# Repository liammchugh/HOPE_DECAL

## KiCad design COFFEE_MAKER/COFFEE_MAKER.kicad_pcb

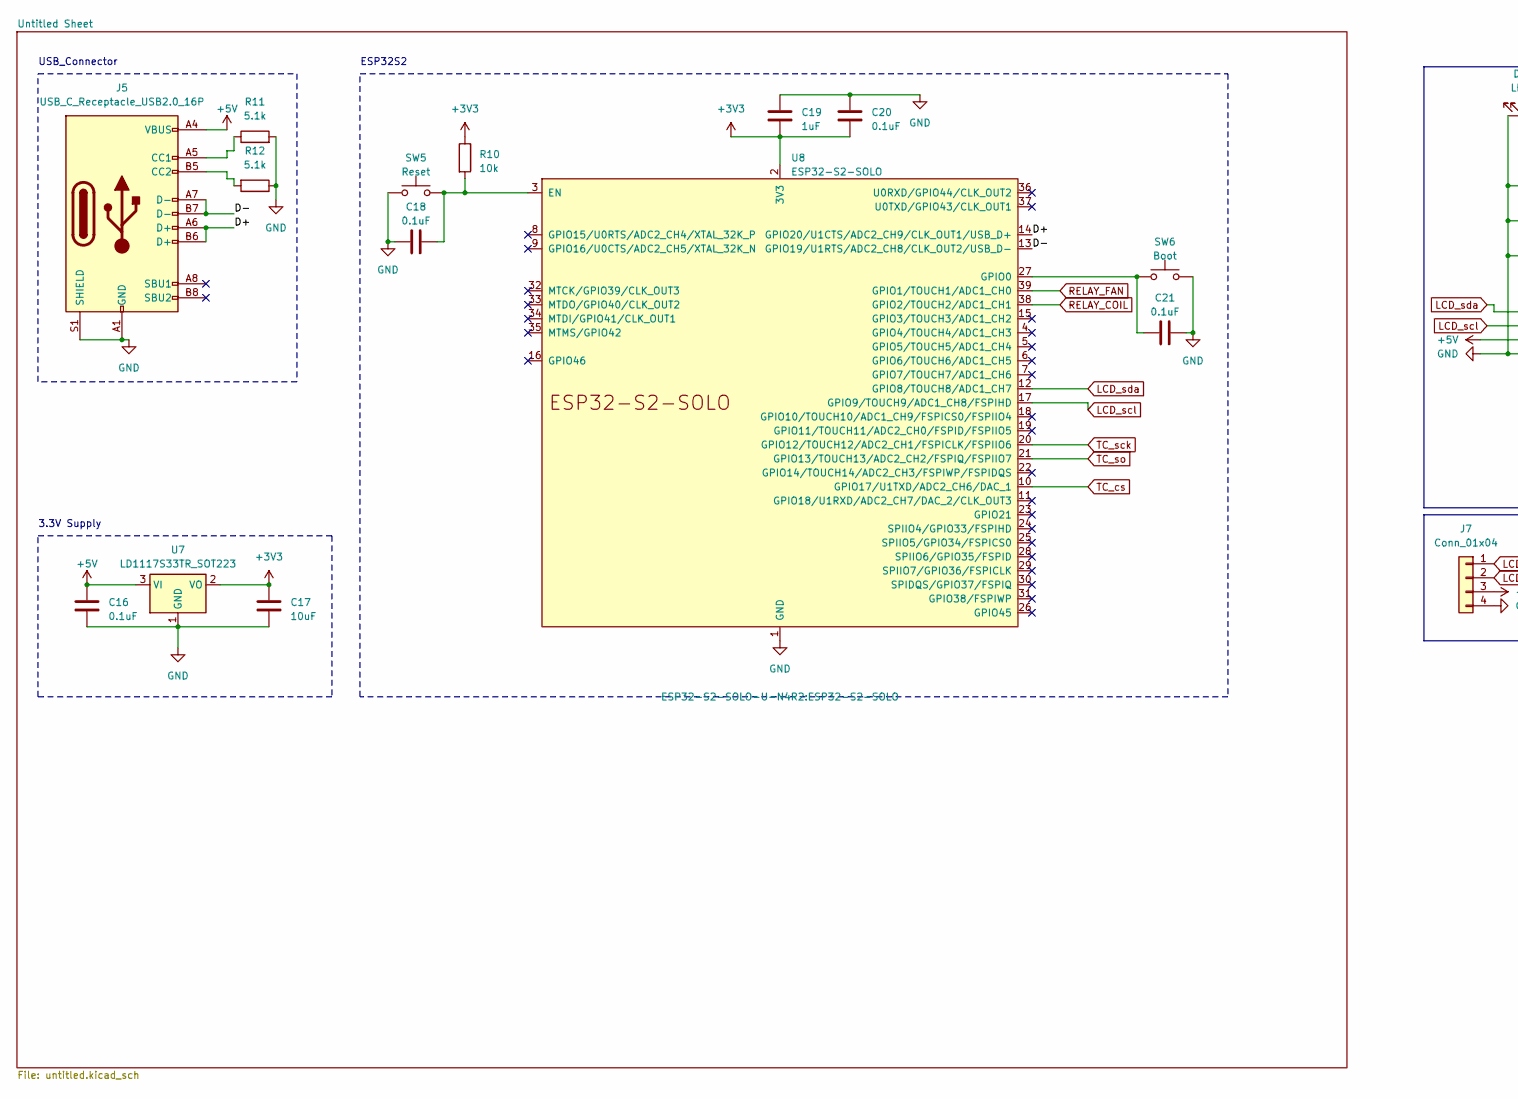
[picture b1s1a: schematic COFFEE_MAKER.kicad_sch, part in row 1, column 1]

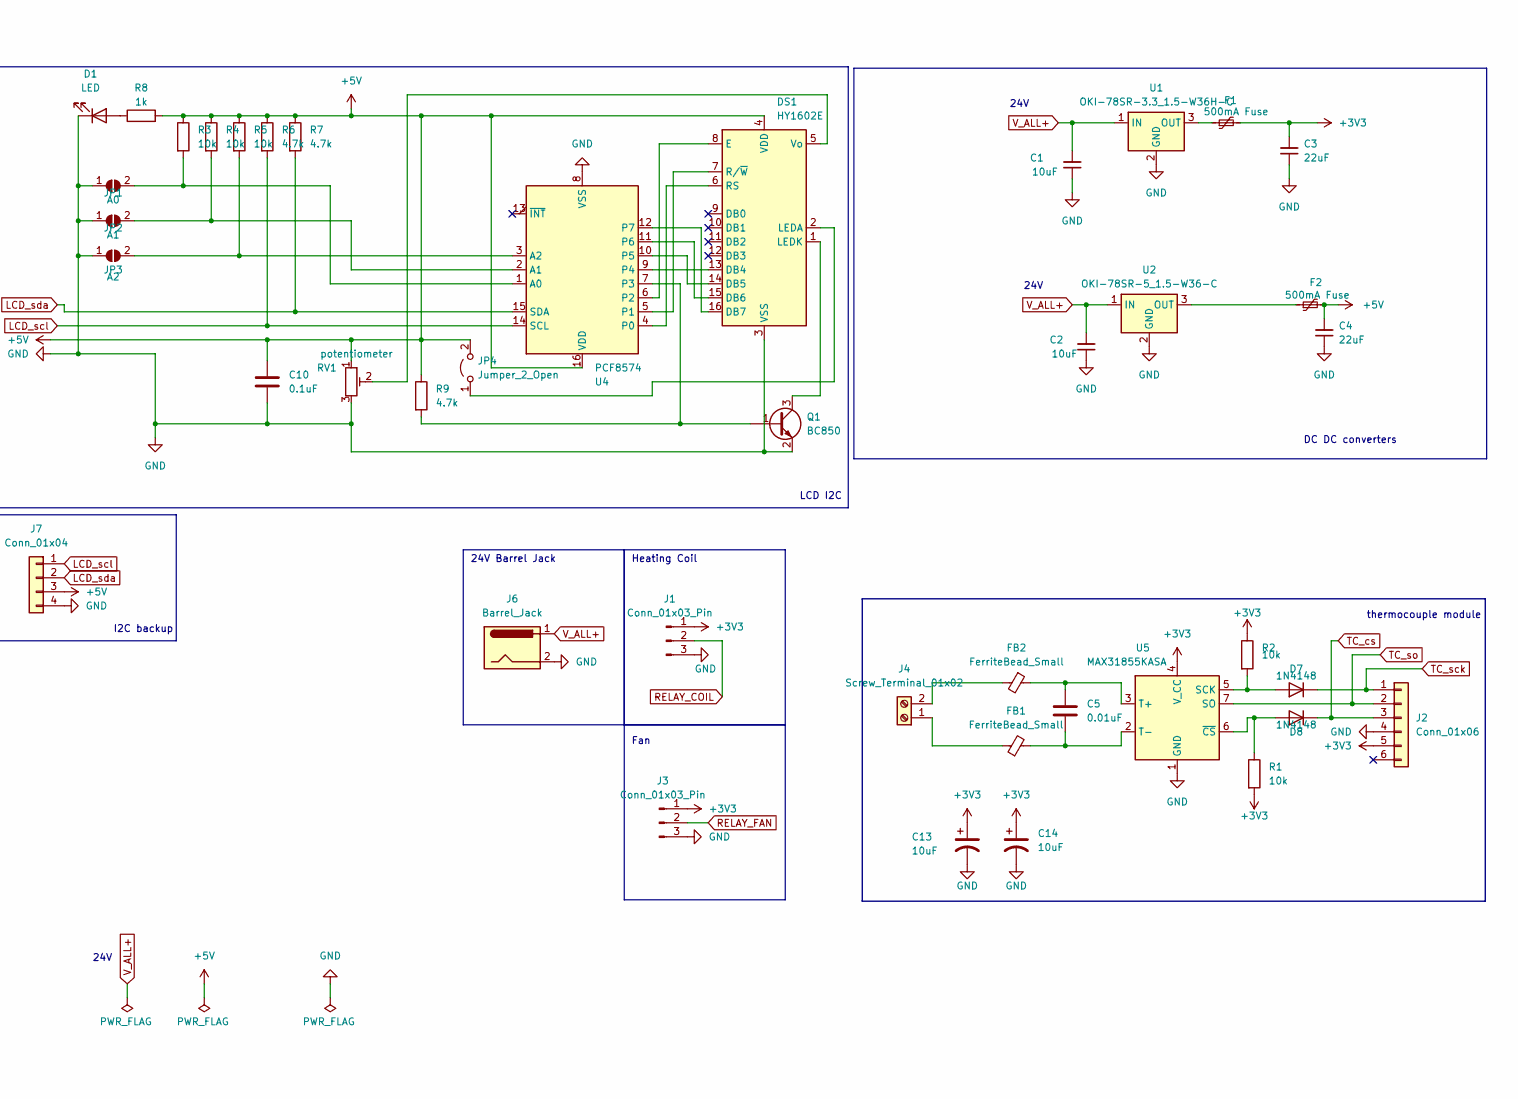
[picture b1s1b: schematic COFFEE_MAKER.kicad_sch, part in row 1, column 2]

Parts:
C1, C2, C13, C14, C17: 10uF; C_0805_2012Metric
C3, C4: 22uF; C_0603_1608Metric
C5: 0.01uF; C_0805_2012Metric
C10, C16, C18, C20, C21: 0.1uF; C_0805_2012Metric
C19: 1uF; C_0805_2012Metric
D1: LED; LED_0805_2012Metric
D7, D8: 1N4148; D_DO-35_SOD27_P7.62mm_Horizontal
DS1: HY1602E
F1, F2: 500mA Fuse; Fuse_0603_1608Metric
FB1, FB2: FerriteBead_Small; R_0603_1608Metric
J1, J3: Conn_01x03_Pin; PinHeader_1x03_P2.54mm_Horizontal
J2: Conn_01x06; PinHeader_1x06_P2.54mm_Vertical
J4: Screw_Terminal_01x02; TerminalBlock_MetzConnect_Type094_RT03502HBLU_1x02_P5.00mm_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
J5: USB_C_Receptacle_USB2.0_16P; USB_C_Receptacle_GCT_USB4105-xx-A_16P_TopMnt_Horizontal
J6: Barrel_Jack; BarrelJack_CUI_PJ-102AH_Horizontal
J7: Conn_01x04; PinHeader_1x04_P2.00mm_Vertical
JP1: A0; SolderJumper-2_P1.3mm_Open_RoundedPad1.0x1.5mm
JP2: A1; SolderJumper-2_P1.3mm_Open_RoundedPad1.0x1.5mm
JP3: A2; SolderJumper-2_P1.3mm_Open_RoundedPad1.0x1.5mm
JP4: Jumper_2_Open; SolderJumper-2_P1.3mm_Open_RoundedPad1.0x1.5mm
Q1: BC850; SOT-23
R1, R2, R3, R4, R5, R10: 10k; R_0603_1608Metric
R6, R7, R9: 4.7k; R_0805_2012Metric
R8: 1k; R_0805_2012Metric
R11, R12: 5.1k; R_0805_2012Metric
RV1: potentiometer; Potentiometer_Bourns_TC33X_Vertical
SW5: Reset; SW_SPST_TL3305A
SW6: Boot; SW_SPST_TL3305A
U1: OKI-78SR-3.3_1.5-W36H-C; Converter_DCDC_Murata_OKI-78SR_Horizontal
U2: OKI-78SR-5_1.5-W36-C; Converter_DCDC_Murata_OKI-78SR_Horizontal
U4: PCF8574; SOIC16R
U5: MAX31855KASA; SOIC-8_3.9x4.9mm_P1.27mm
U7: LD1117S33TR_SOT223; SOT-223-3_TabPin2
U8: ESP32-S2-SOLO

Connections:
+3V3: C3.2, C13.1, C14.1, C17.1, C19.2, C20.2, F1.2, J1.1, J2.5, J3.1, R1.2, R2.1, R10.1, U5.4 (V_CC), U7.2 (VO), U8.2 (3V3)
+5V: C4.2, C10.1, C16.1, DS1.4 (VDD), F2.2, J5.A4 (VBUS), J5.A9 (VBUS), J5.B4 (VBUS), J5.B9 (VBUS), J7.3, JP4.2 (B), R3.1, R4.1, R5.1, R6.1, R7.1, R8.2, R9.1, RV1.1, U4.16 (VDD), U7.3 (VI)
/D+: J5.A6 (D+), J5.B6 (D+), U8.14 (GPIO20/U1CTS/ADC2_CH9/CLK_OUT1/USB_D+)
/D-: J5.A7 (D-), J5.B7 (D-), U8.13 (GPIO19/U1RTS/ADC2_CH8/CLK_OUT2/USB_D-)
GND: C1.1, C2.1, C3.1, C4.1, C10.2, C13.2, C14.2, C16.2, C17.2, C18.1, C19.1, C20.1, C21.2, D1.1 (K), DS1.3 (VSS), J1.3, J2.4, J3.3, J5.A1 (GND), J5.A12 (GND), J5.B1 (GND), J5.B12 (GND), J5.S1 (SHIELD), J6.2, J7.4, JP1.1 (A), JP2.1 (A), JP3.1 (A), Q1.2 (E), R11.2, R12.1, RV1.3, SW5.1, SW6.2, U1.2 (GND), U2.2 (GND), U4.8 (VSS), U5.1 (GND), U7.1 (GND), U8.1 (GND), U8.40 (GND), U8.41 (GND)
LCD_scl: J7.1, R6.2, U4.14 (SCL), U8.17 (GPIO9/TOUCH9/ADC1_CH8/FSPIHD)
LCD_sda: J7.2, R7.2, U4.15 (SDA), U8.12 (GPIO8/TOUCH8/ADC1_CH7)
unnamed: D1.2 (A), R8.1
unnamed: D7.2 (A), R2.2, U5.5 (SCK)
unnamed: D8.2 (A), R1.1, U5.6 (~CS)
unnamed: DS1.13 (DB4), U4.9 (P4)
unnamed: DS1.14 (DB5), U4.10 (P5)
unnamed: DS1.15 (DB6), U4.11 (P6)
unnamed: DS1.16 (DB7), U4.12 (P7)
unnamed: DS1.8 (E), U4.6 (P2)
unnamed: DS1.2 (LEDA), JP4.1 (A)
unnamed: DS1.1 (LEDK), Q1.3 (C)
unnamed: DS1.6 (RS), U4.4 (P0)
unnamed: DS1.7 (R/~W), U4.5 (P1)
unnamed: DS1.5 (Vo), RV1.2
unnamed: FB1.1, J4.1
unnamed: FB2.2, J4.2
unnamed: J5.A5 (CC1), R11.1
unnamed: J5.B5 (CC2), R12.2
unnamed: JP1.2 (B), R3.2, U4.1 (A0)
unnamed: JP2.2 (B), R4.2, U4.2 (A1)
unnamed: JP3.2 (B), R5.2, U4.3 (A2)
unnamed: Q1.1 (B), R9.2, U4.7 (P3)
unnamed: F1.1, U1.3 (OUT)
unnamed: F2.1, U2.3 (OUT)
unnamed: C5.1, FB2.1, U5.3 (T+)
unnamed: C5.2, FB1.2, U5.2 (T-)
unnamed: C18.2, R10.2, SW5.2, U8.3 (EN)
unnamed: C21.1, SW6.1, U8.27 (GPIO0)
RELAY_COIL: J1.2, U8.38 (GPIO2/TOUCH2/ADC1_CH1)
RELAY_FAN: J3.2, U8.39 (GPIO1/TOUCH1/ADC1_CH0)
TC_cs: D8.1 (K), J2.3, U8.10 (GPIO17/U1TXD/ADC2_CH6/DAC_1)
TC_sck: D7.1 (K), J2.1, U8.20 (GPIO12/TOUCH12/ADC2_CH1/FSPICLK/FSPIIO6)
TC_so: J2.2, U5.7 (SO), U8.21 (GPIO13/TOUCH13/ADC2_CH2/FSPIQ/FSPIIO7)
V_ALL+: C1.2, C2.2, J6.1, U1.1 (IN), U2.1 (IN)

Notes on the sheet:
24V
Heating Coil
24V Barrel Jack
LCD I2C
I2C backup
DC DC converters
USB_Connector
thermocouple module
3.3V Supply
Fan
ESP32S2

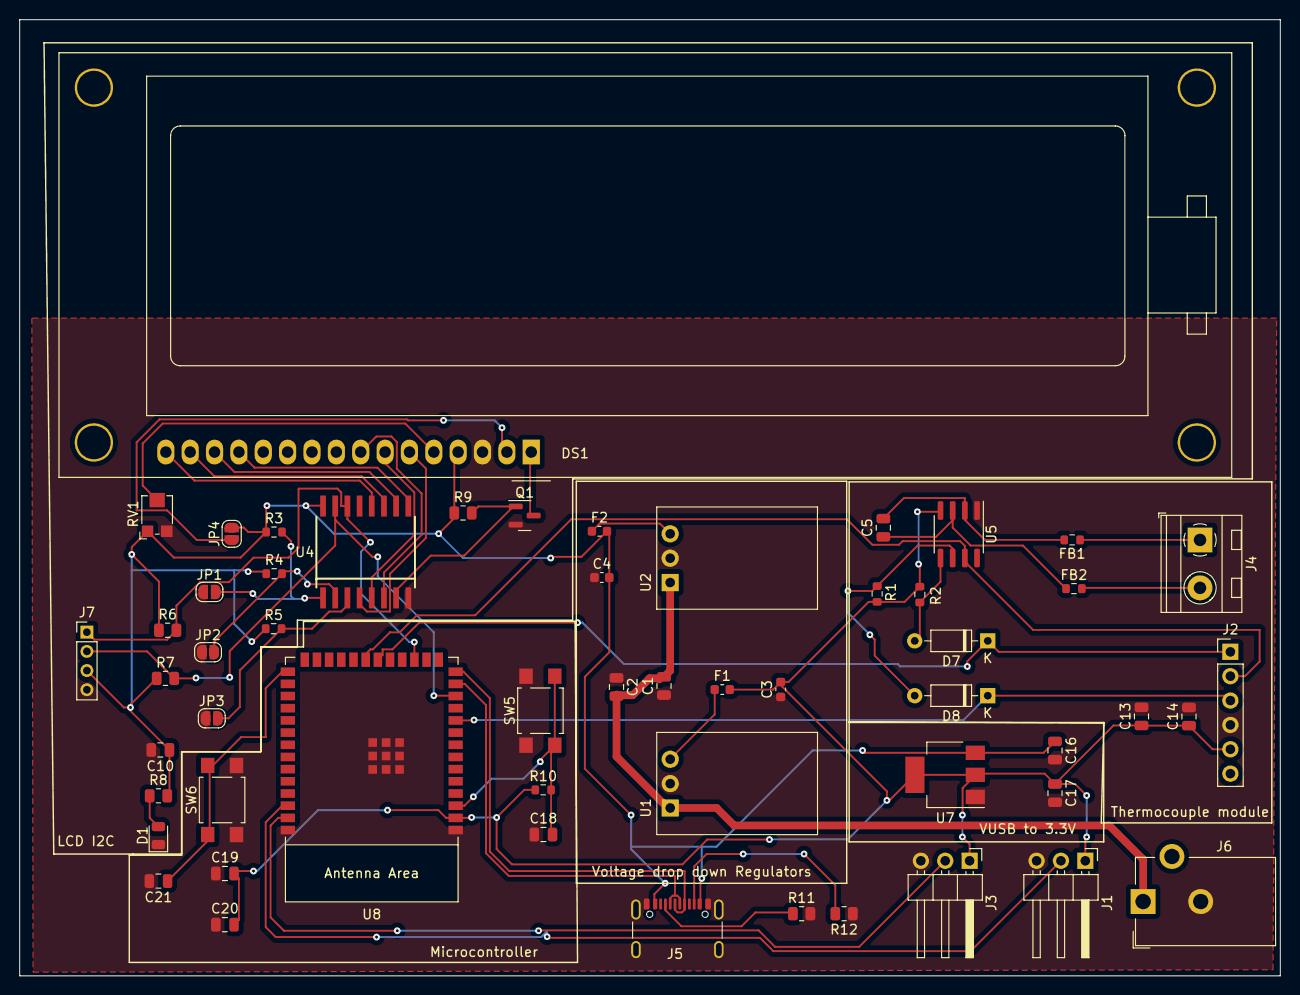
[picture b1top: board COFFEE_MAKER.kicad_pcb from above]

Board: 2 copper layers, 131.4 x 99.7 mm, 55 parts (0 on the bottom side), 40 nets.

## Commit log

2024-03-14 setup and breakout
2024-03-14 update accuracy
2024-03-14 Added Untitled Diagram.drawio
2024-03-14 Added Coffee_HighLevel.drawio
2024-04-03 commits
2024-04-03 updated schematics
2024-04-03 schemativs update
2024-04-04 schematics update
2024-04-04 schematic update
2024-04-04 added backup i2c pin, change lcd voltage to 5v
2024-04-04 added connector for pin
2024-04-04 relay pcb folder
2024-04-05 schematic footprints assigned
2024-04-05 schematics done (custom footprint PCF8574 and ESP32-S2-N4)
2024-04-07 update esp32 footprint, layout wip
2024-04-07 board layout wip 27 errors
2024-04-09 layout done, saved copy of slides
    .Layout done, slides saved as ppt and pdf in folder, google slides here:
    https://docs.google.com/presentation/d/1jqAALReZK5NcbOIQpBx0YGVnQ22f8MZOJf6NqvKvuig/edit#slide=id.g26e1c898e73_0_26
2024-04-09 layout mask to silkscreen fix
2024-04-09 schematic bom wip
2024-04-11 layout v1 done, slides, BOM, manufacturing folder ready
2024-04-11 pcb finalized, manufacturing folder finalized, BOM& slides in submission folder finalized
